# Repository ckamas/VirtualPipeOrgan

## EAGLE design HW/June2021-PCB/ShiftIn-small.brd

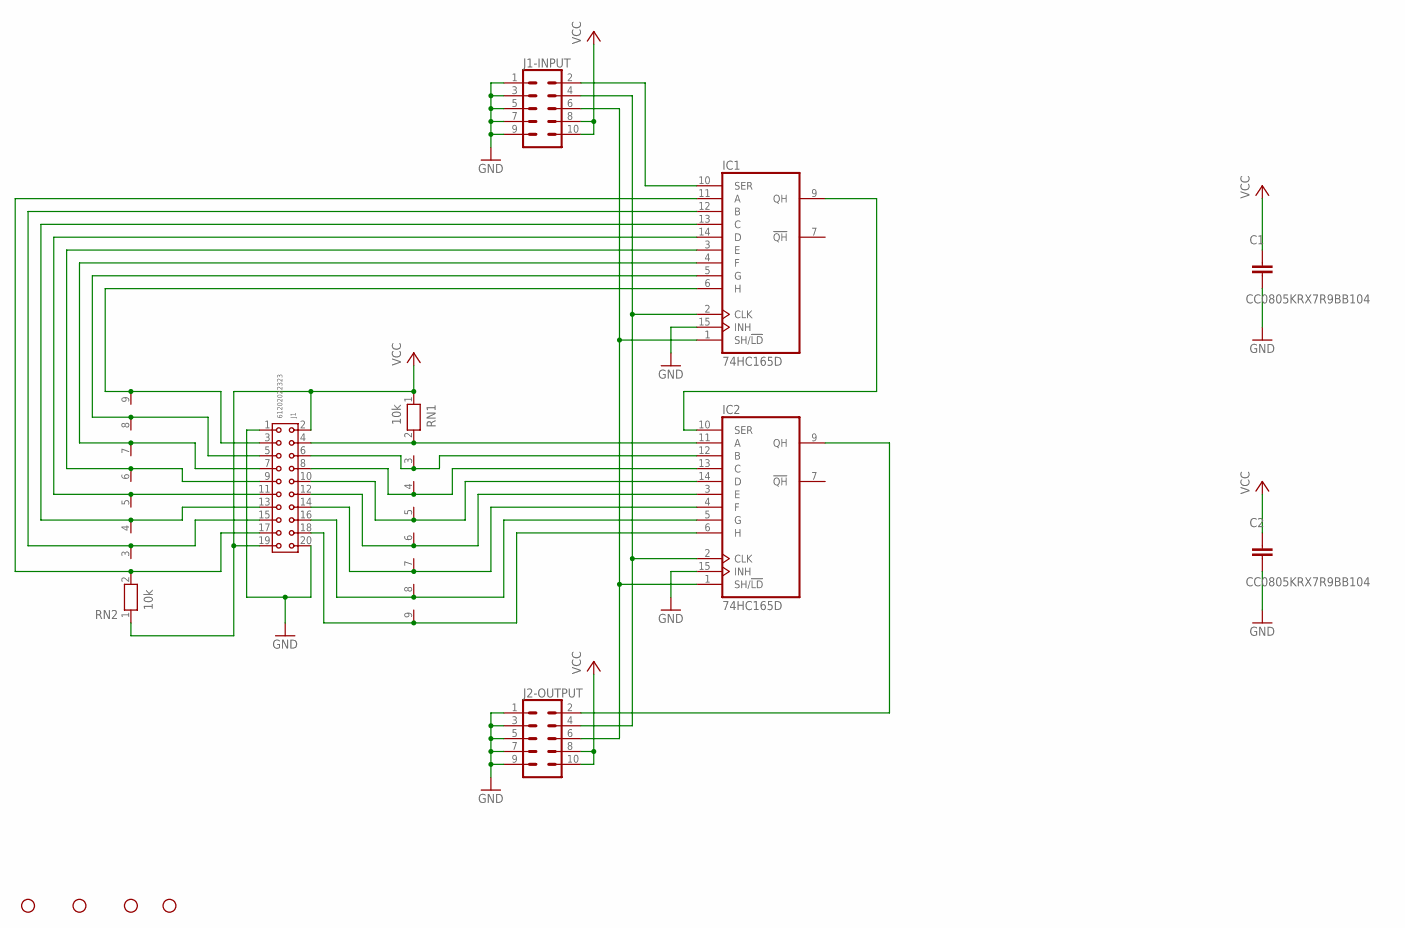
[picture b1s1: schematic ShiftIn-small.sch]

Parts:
C1, C2: CC0805KRX7R9BB104; CAP_0805
H1, H2, H3, H4: STAND-OFF
IC1, IC2: 74HC165D; SO16
J1: 61202022323
J1-INPUT, J2-OUTPUT: CONN_05X2SHD_LOCK; 2X5-SHROUDED_LOCK
RN1, RN2: 10k; RN-9

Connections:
GND: C1.2, C2.2, IC1.8 (GND), IC1.15 (INH), IC2.8 (GND), IC2.15 (INH), J1.1, J1.20, J1-INPUT.1, J1-INPUT.3, J1-INPUT.5, J1-INPUT.7, J1-INPUT.9, J2-OUTPUT.1, J2-OUTPUT.3, J2-OUTPUT.5, J2-OUTPUT.7, J2-OUTPUT.9
unnamed: IC1.2 (CLK), IC2.2 (CLK), J1-INPUT.4, J2-OUTPUT.4
unnamed: IC1.9 (QH), IC2.10 (SER)
unnamed: IC1.10 (SER), J1-INPUT.2
unnamed: IC1.11 (A), J1.17, RN2.2
unnamed: IC2.9 (QH), J2-OUTPUT.2
unnamed: IC1.12 (B), J1.15, RN2.3
unnamed: IC1.13 (C), J1.13, RN2.4
unnamed: IC1.14 (D), J1.11, RN2.5
unnamed: IC1.3 (E), J1.9, RN2.6
unnamed: IC1.4 (F), J1.7, RN2.7
unnamed: IC1.5 (G), J1.5, RN2.8
unnamed: IC1.6 (H), J1.3, RN2.9
unnamed: IC2.11 (A), J1.4, RN1.2
unnamed: IC2.12 (B), J1.6, RN1.3
unnamed: IC2.13 (C), J1.8, RN1.4
unnamed: IC2.14 (D), J1.10, RN1.5
unnamed: IC2.3 (E), J1.12, RN1.6
unnamed: IC2.4 (F), J1.14, RN1.7
unnamed: IC2.5 (G), J1.16, RN1.8
unnamed: IC2.6 (H), J1.18, RN1.9
unnamed: IC1.1 (SH/!LD), IC2.1 (SH/!LD), J1-INPUT.6, J2-OUTPUT.6
VCC: C1.1, C2.1, IC1.16 (VCC), IC2.16 (VCC), J1.2, J1.19, J1-INPUT.8, J1-INPUT.10, J2-OUTPUT.8, J2-OUTPUT.10, RN1.1, RN2.1

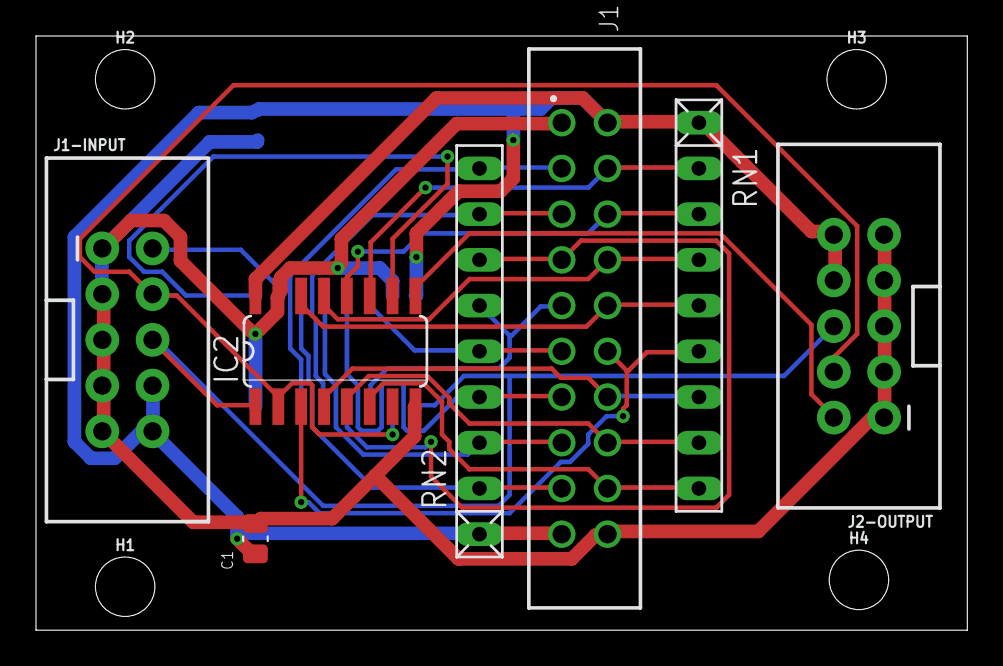
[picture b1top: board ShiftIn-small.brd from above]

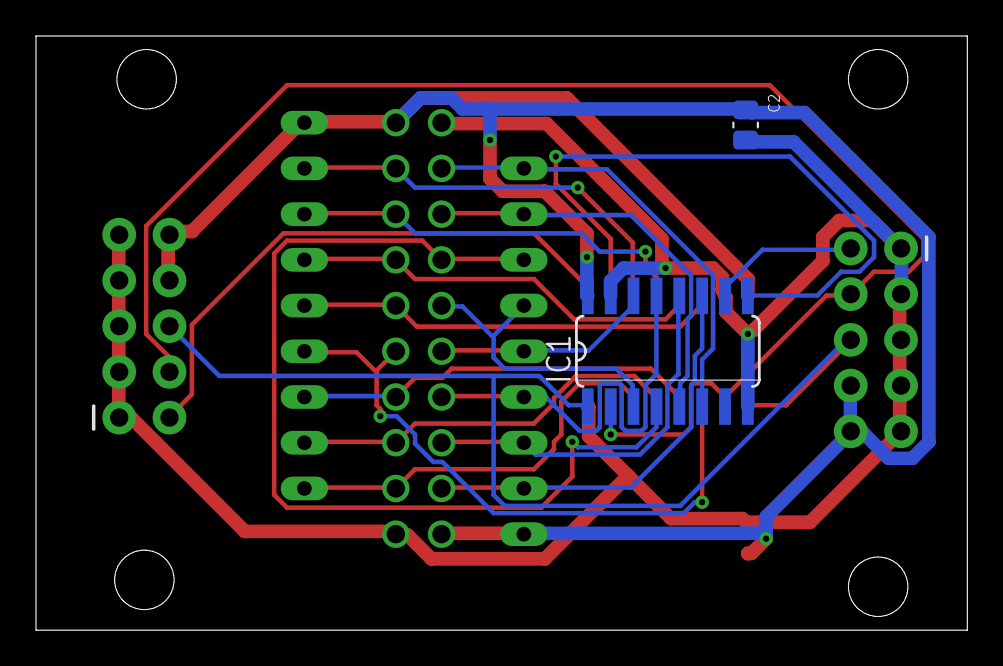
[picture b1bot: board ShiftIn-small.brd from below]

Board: 2 copper layers, 51.7 x 33.0 mm, 13 parts (2 on the bottom side), 23 nets.

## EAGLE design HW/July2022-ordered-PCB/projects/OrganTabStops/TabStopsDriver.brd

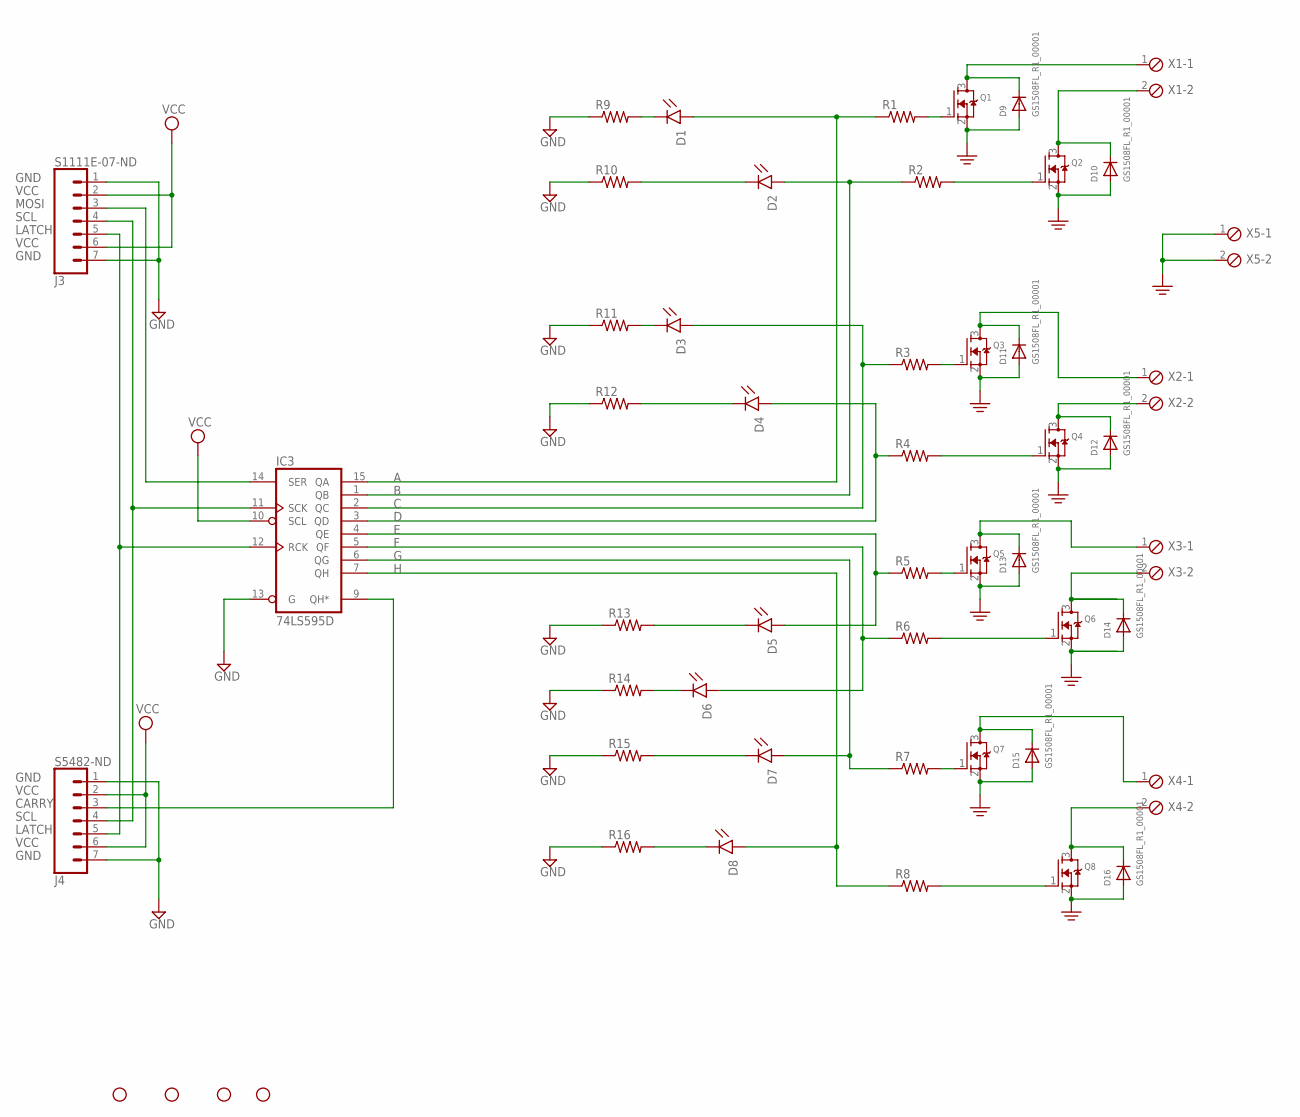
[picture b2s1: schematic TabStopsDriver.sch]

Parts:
D1, D2, D3, D4, D5, D6, D7, D8: B1911NB--20C005314U1930; LEDC1608X95N_RND-R
D9, D10, D11, D12, D13, D14, D15, D16: GS1508FL_R1_00001; SOD-123FL
H1, H2, H3, H4: STAND-OFF
IC3: 74LS595D; SO16
J3: S1111E-07-ND; 1X07_LONGPADS
J4: S5482-ND; 1X07_LONGPADS
Q1, Q2, Q3, Q4, Q5, Q6, Q7, Q8: 3757-PJA3416A_R1_00001CT-ND; SOT23
R1, R2, R3, R4, R5, R6, R7, R8: RMCF0805FT100RCT-ND; R0805
R9, R10, R11, R12, R13, R14, R15, R16: RMCF0805FT1K50CT-ND; R0805
X1, X2, X3, X4, X5: 277-6156-ND; 2POL254

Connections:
A: D1.A, IC3.15 (QA), R1.1
B: D2.A, IC3.1 (QB), R2.1
C: D3.A, IC3.2 (QC), R3.1
CARRY: IC3.9 (QH*), J4.3
D: D4.A, IC3.3 (QD), R4.1
E: D5.A, IC3.4 (QE), R5.1
EGND: D9.A, D10.A, D11.A, D12.A, D13.A, D14.A, D15.A, D16.A, Q1.2 (S), Q2.2 (S), Q3.2 (S), Q4.2 (S), Q5.2 (S), Q6.2 (S), Q7.2 (S), Q8.2 (S), X5.1, X5.2
F: D6.A, IC3.5 (QF), R6.1
G: D7.A, IC3.6 (QG), R7.1
GND: IC3.8 (GND), IC3.13 (G), J3.1, J3.7, J4.1, J4.7, R9.1, R10.1, R11.1, R12.1, R13.1, R14.1, R15.1, R16.1
H: D8.A, IC3.7 (QH), R8.1
LATCH: IC3.12 (RCK), J3.5, J4.5
MOSI: IC3.14 (SER), J3.3
unnamed: Q3.1 (G), R3.2
unnamed: Q2.1 (G), R2.2
unnamed: Q1.1 (G), R1.2
unnamed: Q4.1 (G), R4.2
unnamed: Q6.1 (G), R6.2
unnamed: Q5.1 (G), R5.2
unnamed: Q7.1 (G), R7.2
unnamed: Q8.1 (G), R8.2
unnamed: D9.C, Q1.3 (D), X1.1
unnamed: D10.C, Q2.3 (D), X1.2
unnamed: D11.C, Q3.3 (D), X2.1
unnamed: D12.C, Q4.3 (D), X2.2
unnamed: D13.C, Q5.3 (D), X3.1
unnamed: D14.C, Q6.3 (D), X3.2
unnamed: D15.C, Q7.3 (D), X4.1
unnamed: D16.C, Q8.3 (D), X4.2
unnamed: D1.C, R9.2
unnamed: D2.C, R10.2
unnamed: D3.C, R11.2
unnamed: D4.C, R12.2
unnamed: D5.C, R13.2
unnamed: D6.C, R14.2
unnamed: D7.C, R15.2
unnamed: D8.C, R16.2
SCL: IC3.11 (SCK), J3.4, J4.4
VCC: IC3.10 (SCL), IC3.16 (VCC), J3.2, J3.6, J4.2, J4.6

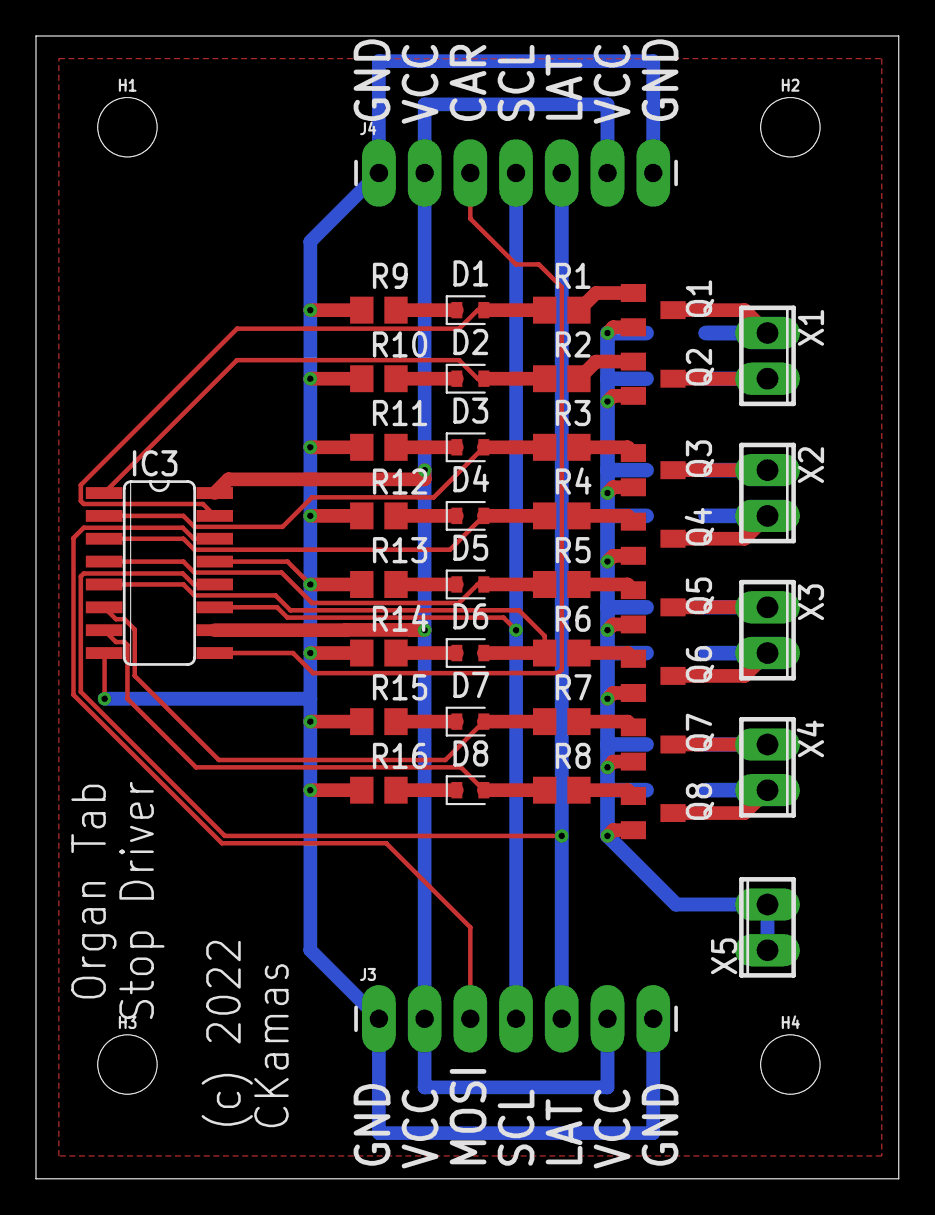
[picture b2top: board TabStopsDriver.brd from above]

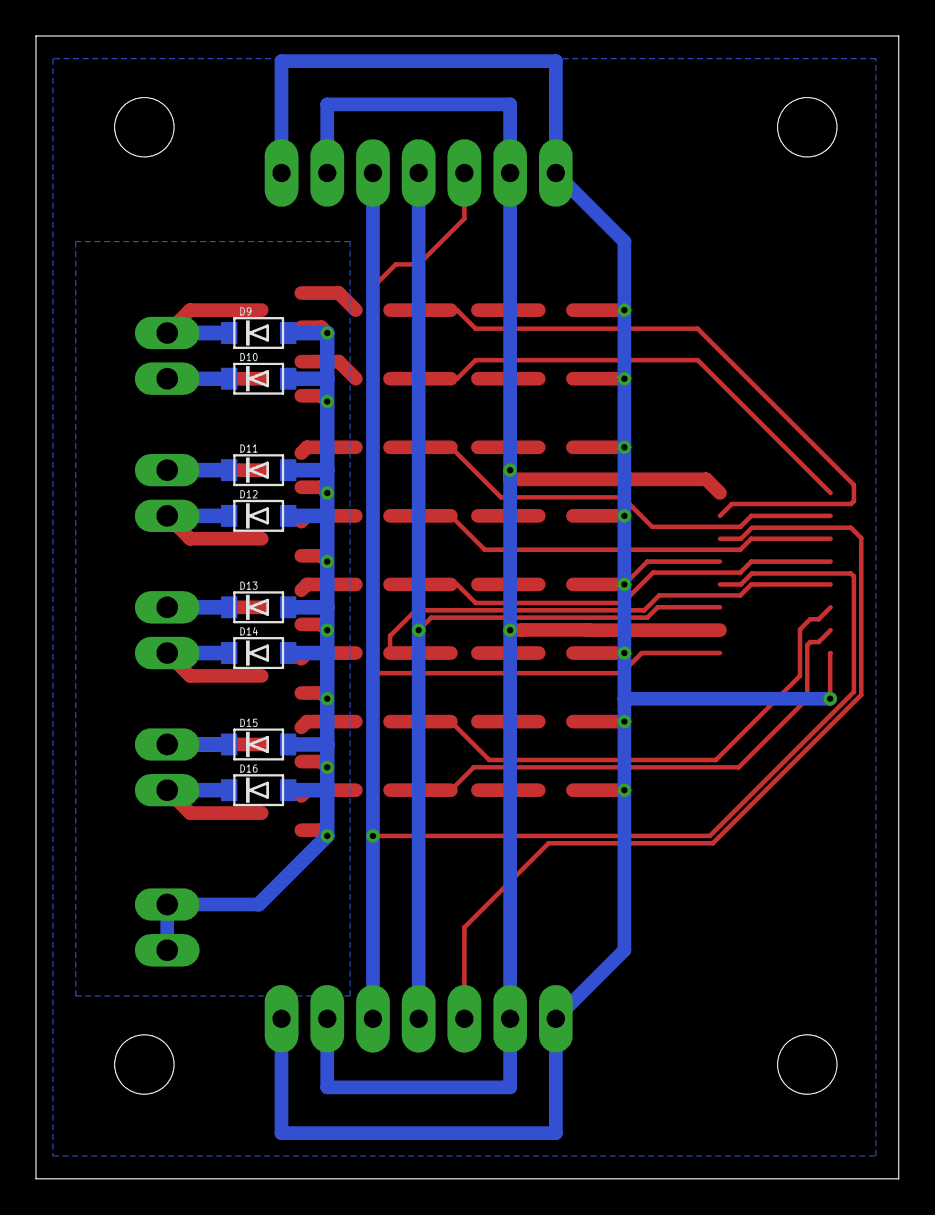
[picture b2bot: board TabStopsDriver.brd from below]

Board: 2 copper layers, 47.9 x 63.5 mm, 52 parts (8 on the bottom side), 39 nets.

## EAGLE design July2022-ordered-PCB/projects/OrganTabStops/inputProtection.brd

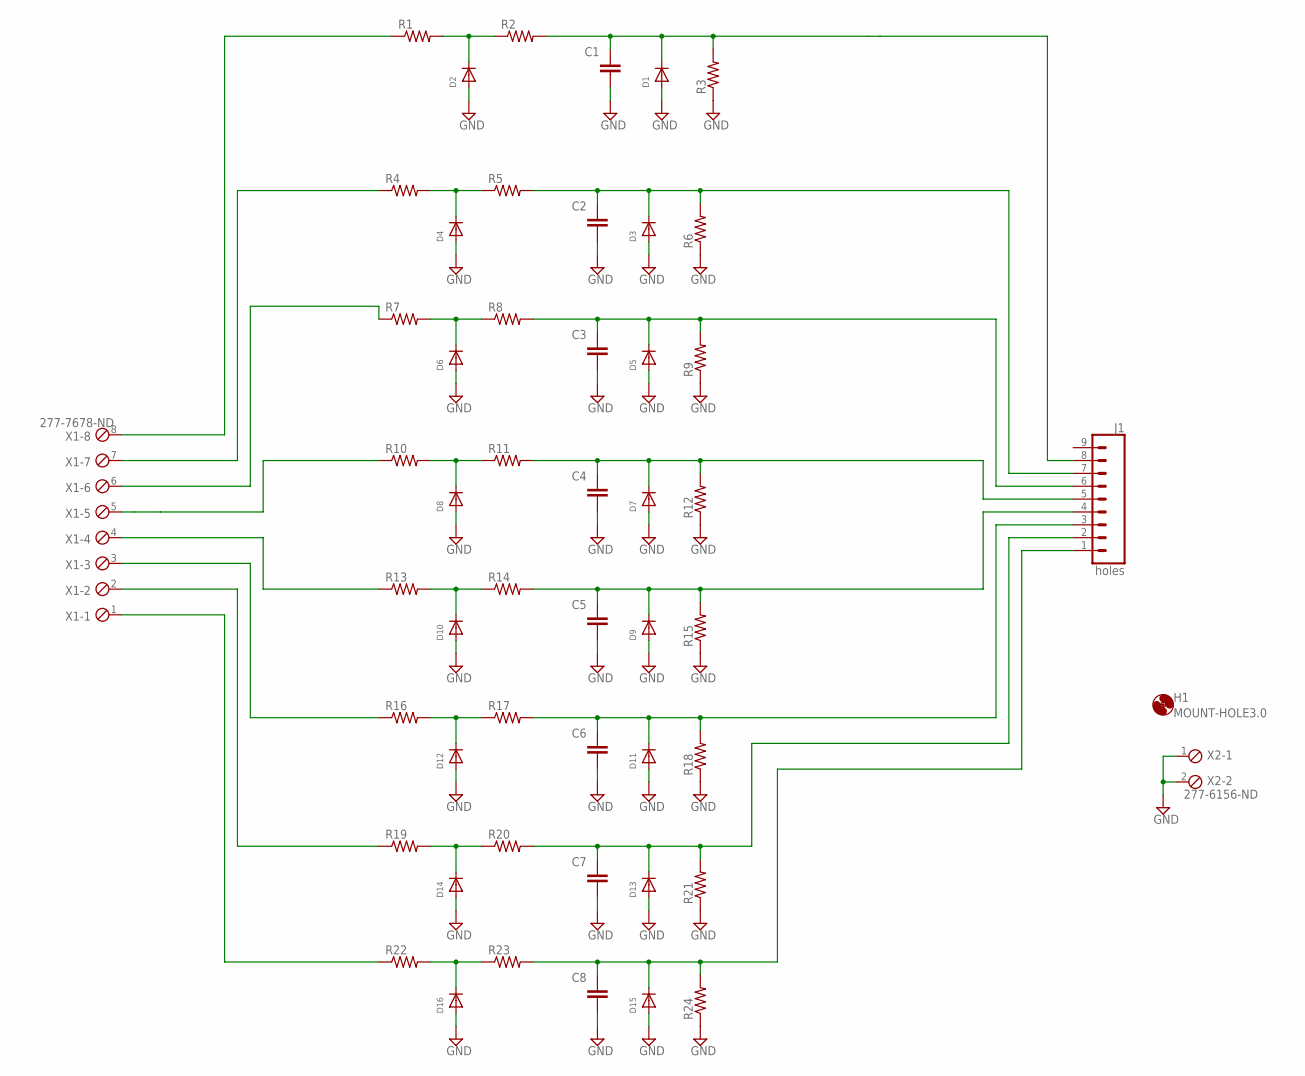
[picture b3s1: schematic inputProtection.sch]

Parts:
C1, C2, C3, C4, C5, C6, C7, C8: CC0805KRX7R9BB104; CAP_0805; MPN ECH-U1C103JX5; DIGIKEY_PART_NUMBER ECH-U1C103JX5
D1, D3, D5, D7, D9, D11, D13, D15: BZT52C4V7-13FDICT-ND; SOD-123
D2, D4, D6, D8, D10, D12, D14, D16: BAS70WS_R1_00001; SOD-323F
H1: MOUNT-HOLE3.0; 3,0
J1: holes; 1X09_LONGPADS
R1, R4, R7, R10, R13, R16, R19, R22: 10 RHM10KCT-ND; R0805
R2, R5, R8, R11, R14, R17, R20, R23: 1k RHM1.0KKCT-ND; R0805
R3, R6, R9, R12, R15, R18, R21, R24: 10k RHM10KKCT-ND; R0805
X1: 277-7678-ND; 8POL254
X2: 277-6156-ND; 2POL254

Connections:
GND: C1.2, C2.2, C3.2, C4.2, C5.2, C6.2, C7.2, C8.2, D1.A, D2.A, D3.A, D4.A, D5.A, D6.A, D7.A, D8.A, D9.A, D10.A, D11.A, D12.A, D13.A, D14.A, D15.A, D16.A, R3.1, R6.1, R9.1, R12.1, R15.1, R18.1, R21.1, R24.1, X2.1, X2.2
unnamed: D2.C, R1.2, R2.1
unnamed: C1.1, D1.C, J1.8, R2.2, R3.2
unnamed: D4.C, R4.2, R5.1
unnamed: C2.1, D3.C, J1.7, R5.2, R6.2
unnamed: D6.C, R7.2, R8.1
unnamed: C3.1, D5.C, J1.6, R8.2, R9.2
unnamed: D8.C, R10.2, R11.1
unnamed: C4.1, D7.C, J1.5, R11.2, R12.2
unnamed: D10.C, R13.2, R14.1
unnamed: C5.1, D9.C, J1.4, R14.2, R15.2
unnamed: D12.C, R16.2, R17.1
unnamed: C6.1, D11.C, J1.3, R17.2, R18.2
unnamed: D14.C, R19.2, R20.1
unnamed: C7.1, D13.C, J1.2, R20.2, R21.2
unnamed: D16.C, R22.2, R23.1
unnamed: C8.1, D15.C, J1.1, R23.2, R24.2
unnamed: R1.1, X1.8
unnamed: R4.1, X1.7
unnamed: R7.1, X1.6
unnamed: R10.1, X1.5
unnamed: R13.1, X1.4
unnamed: R16.1, X1.3
unnamed: R19.1, X1.2
unnamed: R22.1, X1.1

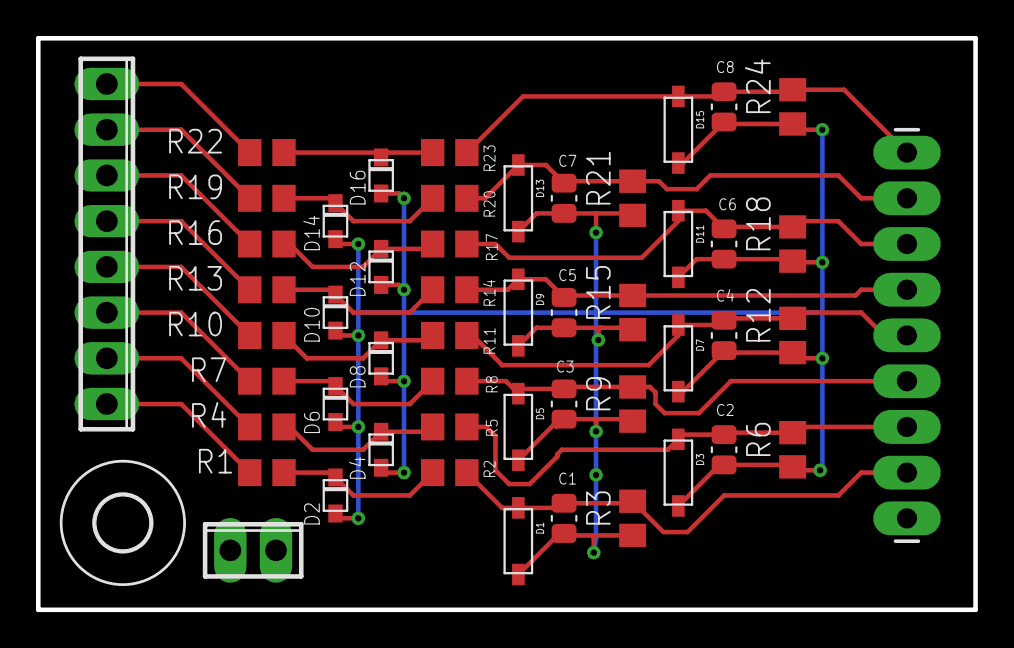
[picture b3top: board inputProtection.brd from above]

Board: 2 copper layers, 52.1 x 31.8 mm, 52 parts (0 on the bottom side), 25 nets.

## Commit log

2023-09-19 adding docs
2023-10-04 updated code to drive tab until switch closure and added schematics and gerbers
    Arduino/TabStops/TabStopMain/TabStopDriver.cpp/.h
    reworked to use index instead of spi #
    removed test code
    Arduino/TabStops/TabStopMain/TabStopMain.ino
    moved data base into its own file
    turned off optimization so I can easly debug
2023-10-09 modified the database
2023-10-13 updated to run the tabs on a state machine
2023-10-21 fixed databse
2023-11-05 reorg directories
2023-11-05 fixup on missing files
2023-11-18 2023 nov 18
2023-11-26 tab stop reader 1st pass
2023-11-30 debounce
    FW/TabStops/TabStopMain/TabStopDataBase.cpp/.h
    added delay for tab key debounce
    FW/TabStops/TabStopMain/TabStopReaderClass.cpp/.hpp
    added debounce
2023-12-12 added light control (only works on sprotszondo :-( )
2024-03-31 update for manual scanner to add pistons
2024-03-31 update manual scanner to scan pistons and remove uin64 which caused variable delays
2024-04-01 asserts and remove 64bits
    Added asserts into ManualScanner.ino and converted from a single
    64 bit int to 4, 16 bit ints. got rid of stalling bug that looked like a
    ~100 ms pause on the scanning
    added code to print out a version and compile data on boot up
2024-04-01 added auto git tagging
2024-04-01 added git version
2024-10-18 Keyboard updates and optimization
    FW/ManualScanner/ManualScanner.ino
    made all of the arrays the same width
    FW/TabStops/TabStopMain/TabStopMain.ino
    added debug code to toggle the tabstops
    FW/TabStops/TabStopMain/TabStopReaderClass.cpp
    removed checking for 0 and setting to 1. Debug code?
2024-10-22 noticed that MyTabReader.loop is taking too long!

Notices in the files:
HW/July2022-ordered-PCB/projects/OrganTabStops/TabStopsDriver.brd:
(c) 2022
parts and their libraries:
SparkFun-Hardware: Licensing: Creative Commons ShareAlike 4.0 International - https://creativecommons.org/licenses/by-sa/4.0
Wurth_Connectors_WR-BHD: Copyright: Würth Elektronik
